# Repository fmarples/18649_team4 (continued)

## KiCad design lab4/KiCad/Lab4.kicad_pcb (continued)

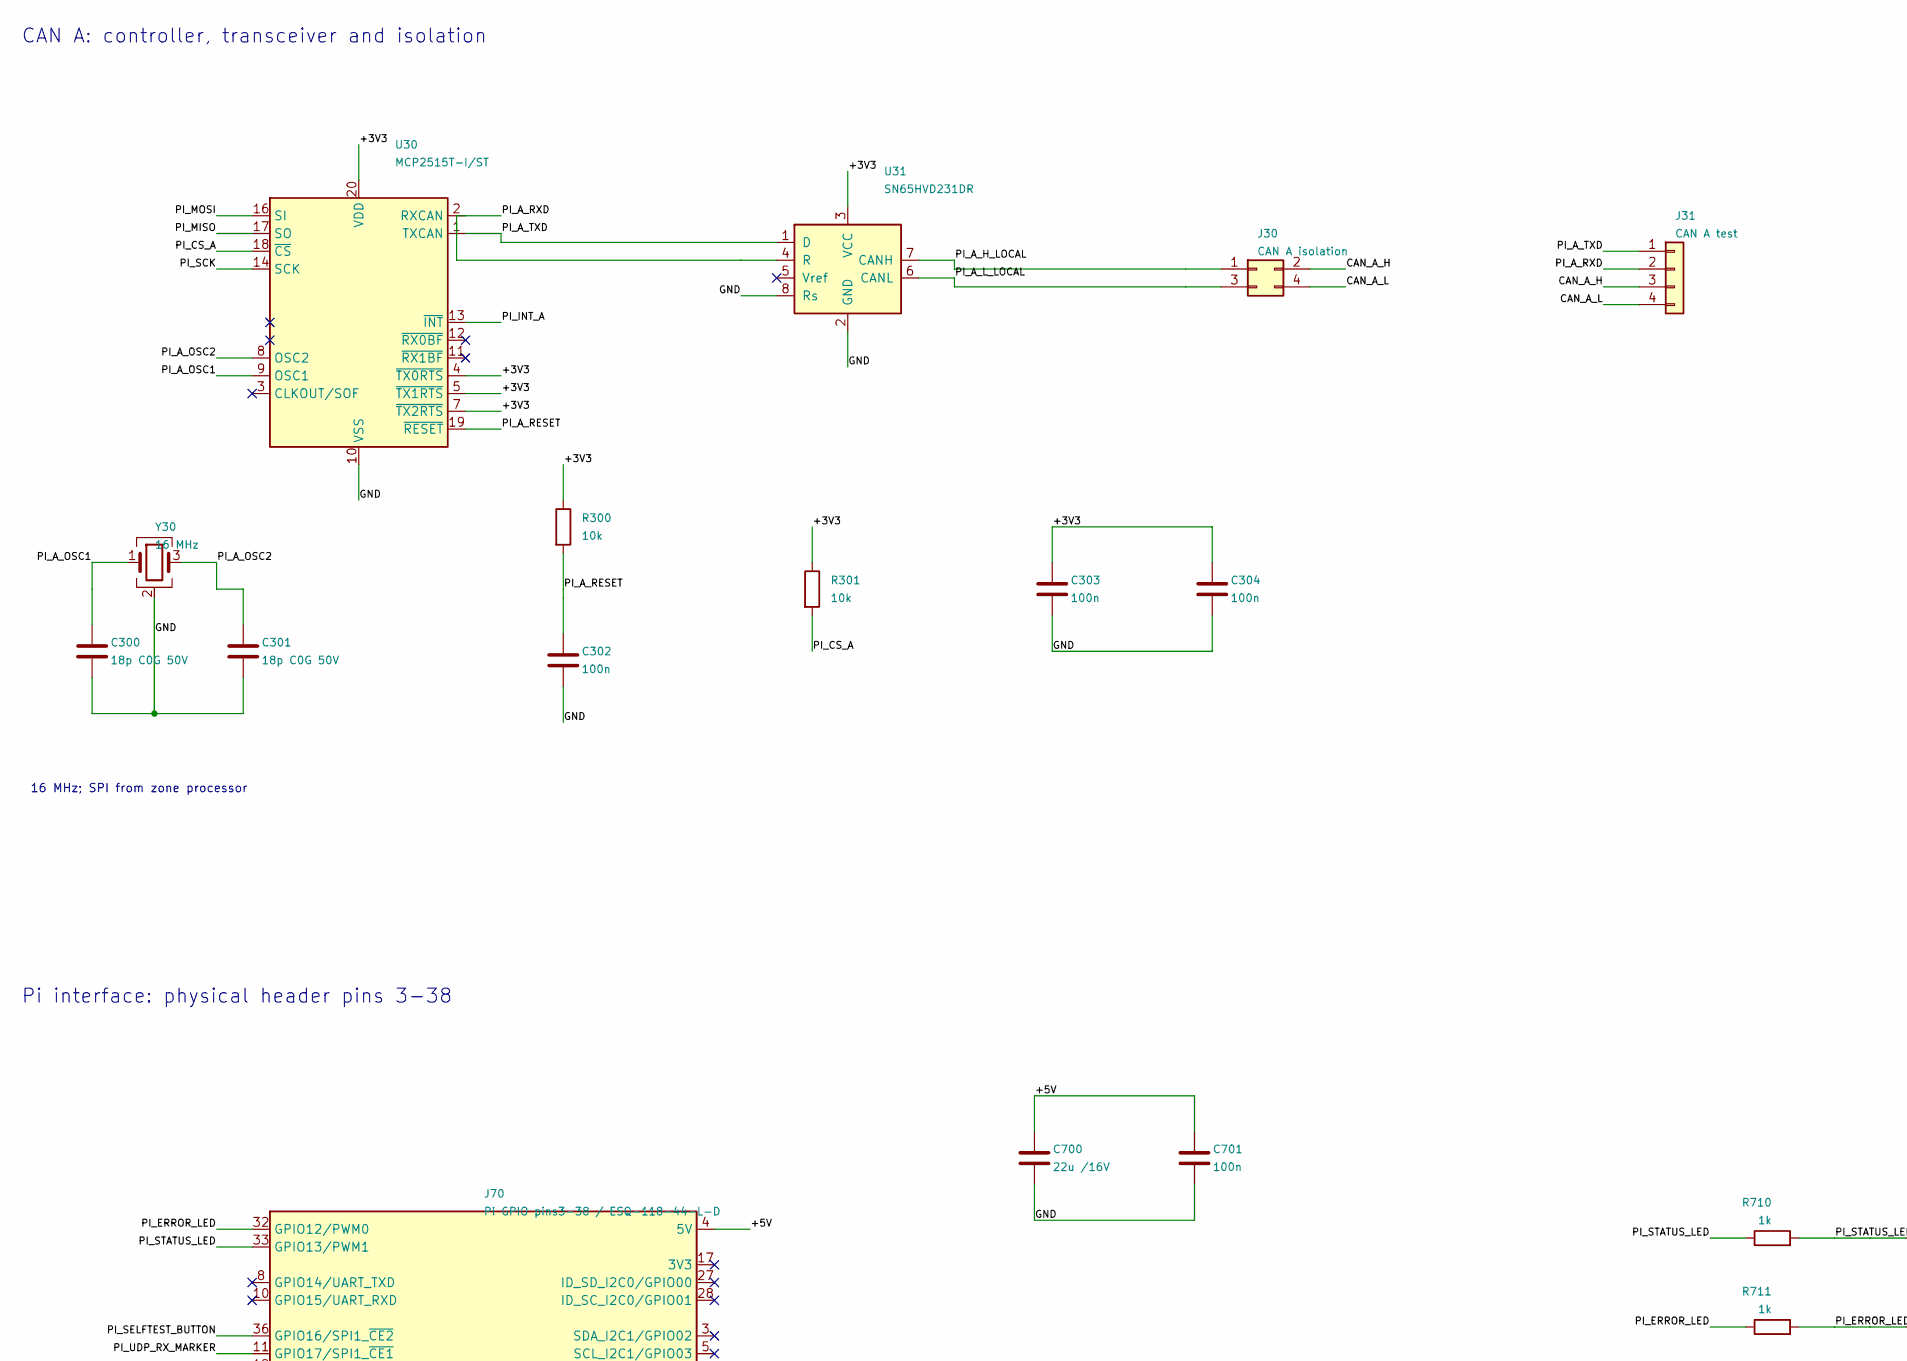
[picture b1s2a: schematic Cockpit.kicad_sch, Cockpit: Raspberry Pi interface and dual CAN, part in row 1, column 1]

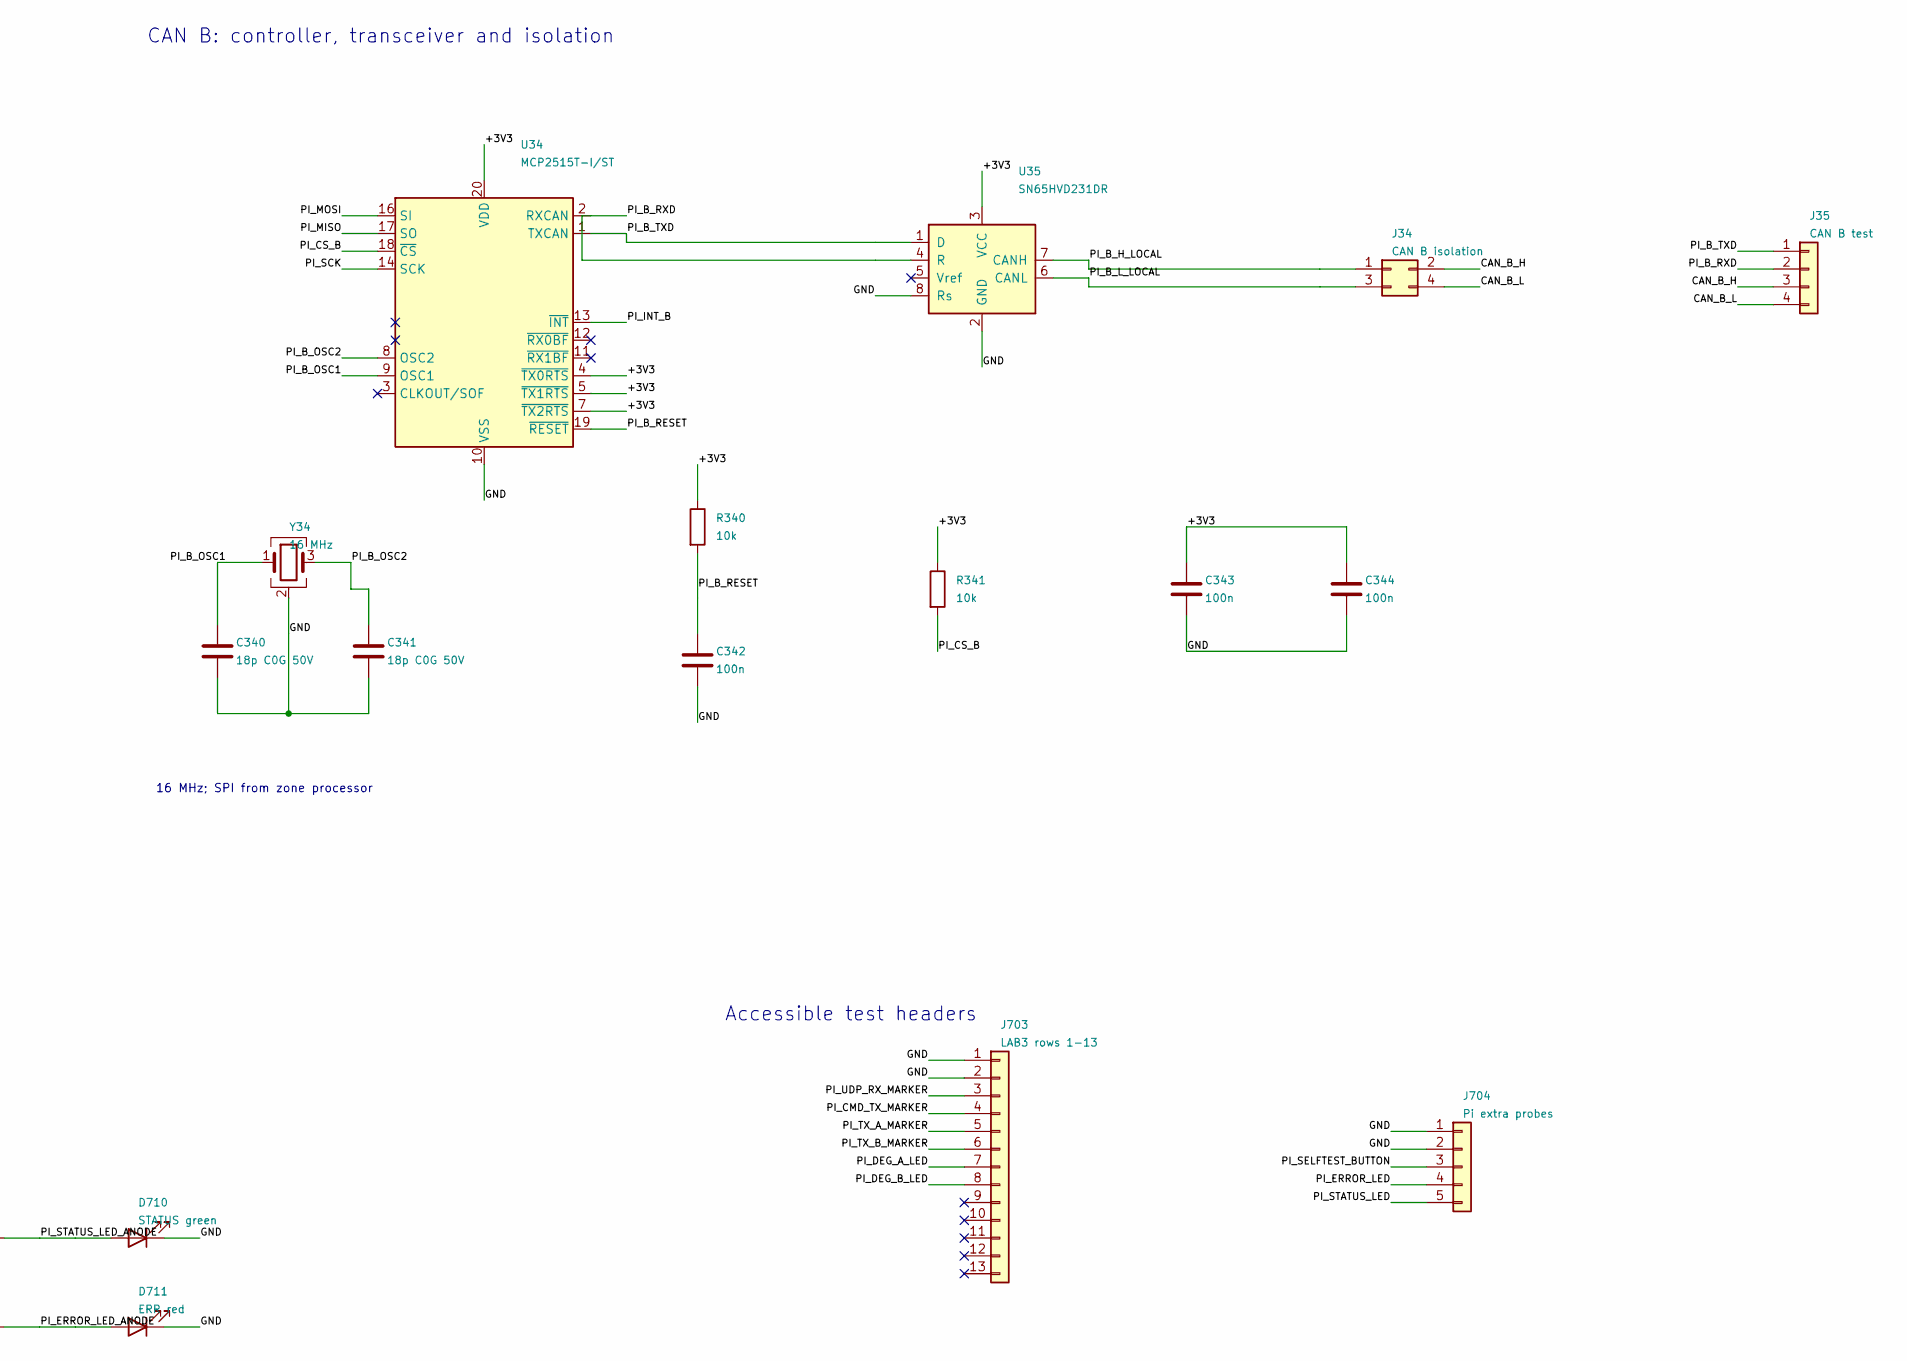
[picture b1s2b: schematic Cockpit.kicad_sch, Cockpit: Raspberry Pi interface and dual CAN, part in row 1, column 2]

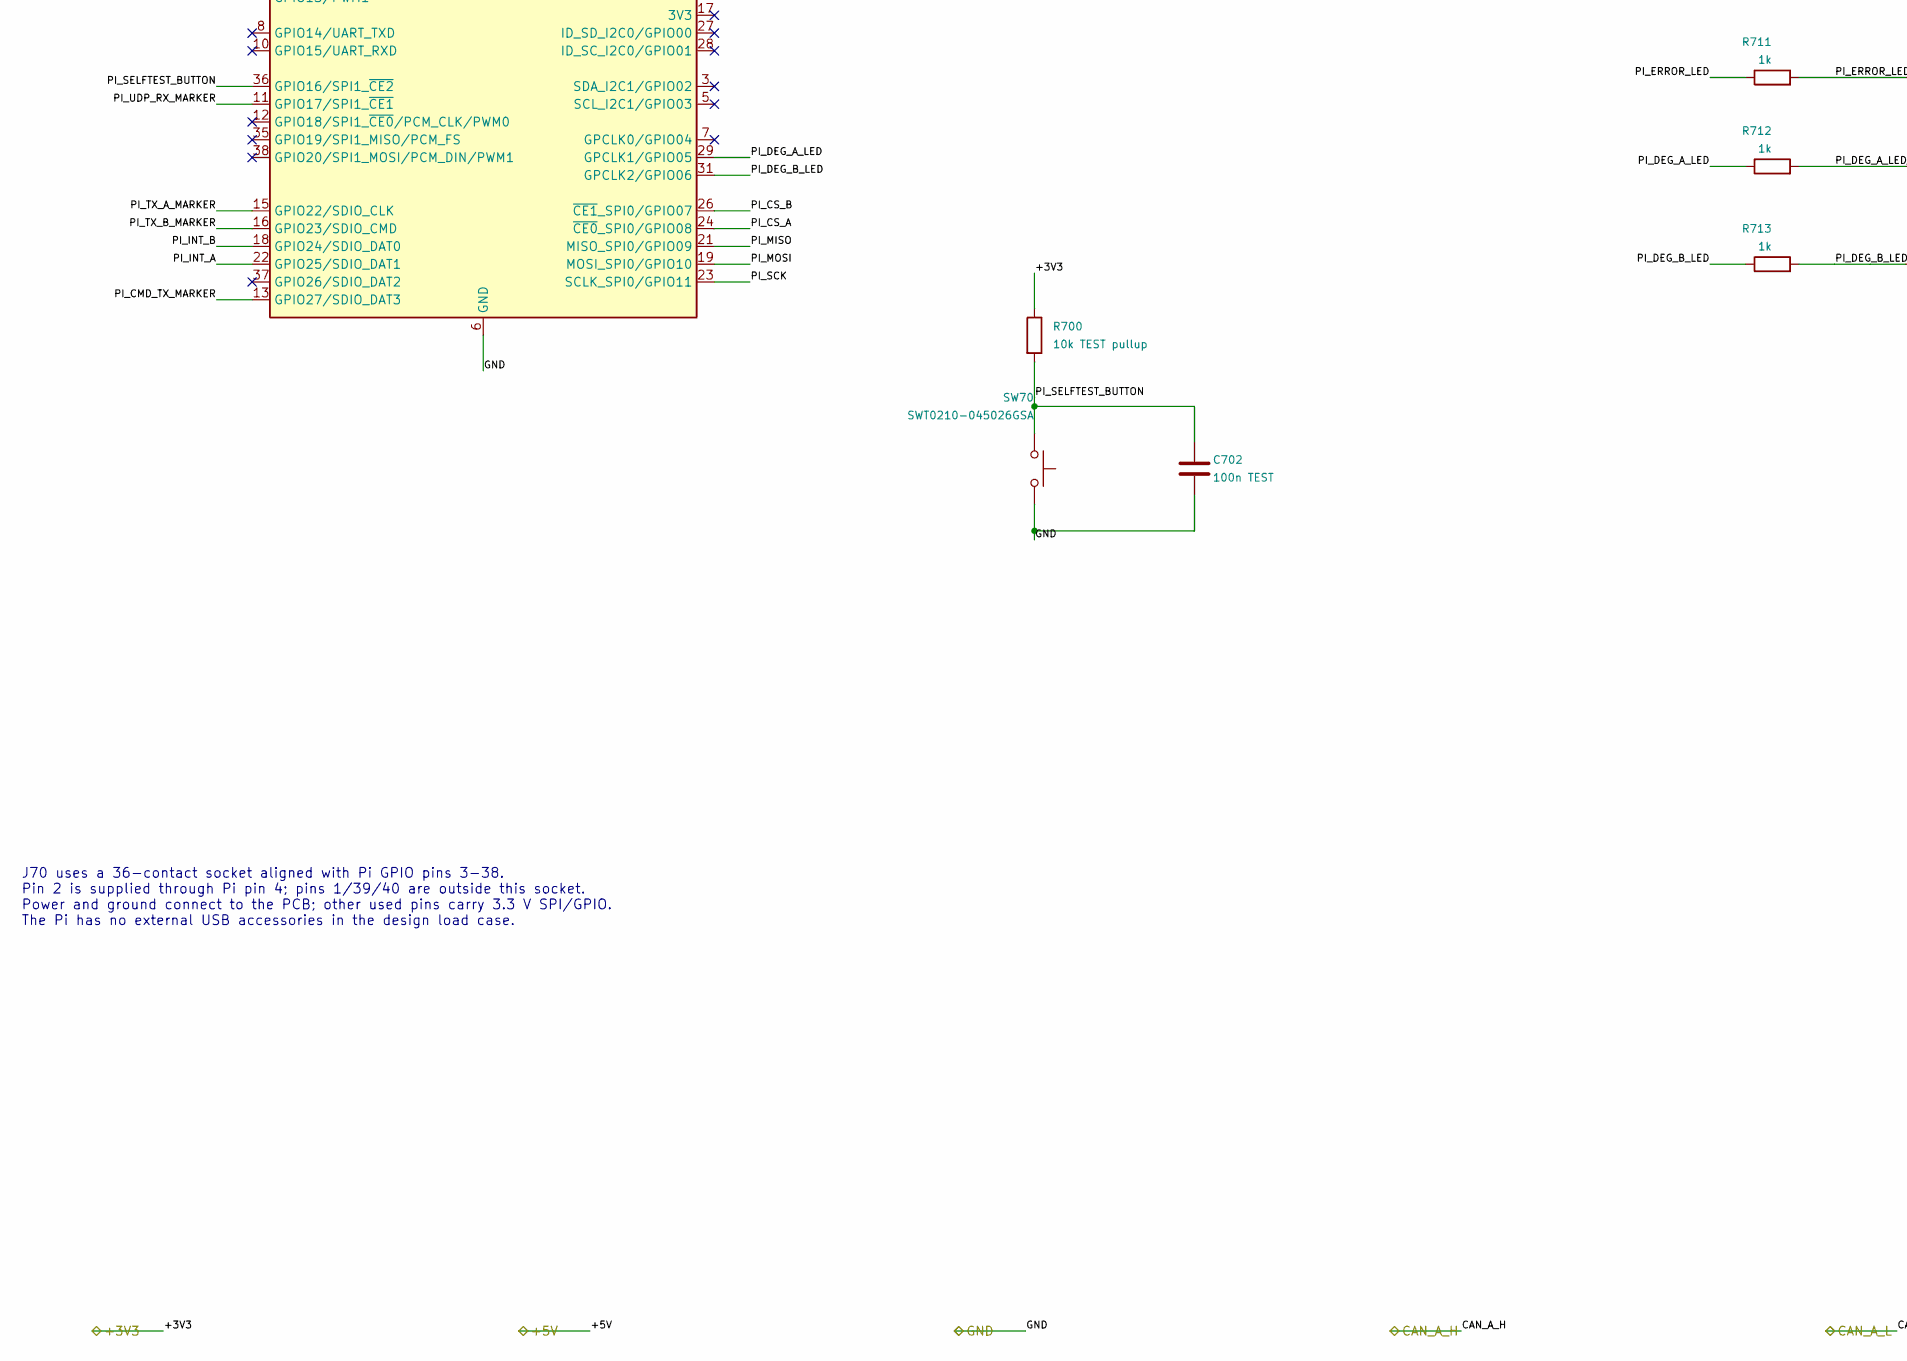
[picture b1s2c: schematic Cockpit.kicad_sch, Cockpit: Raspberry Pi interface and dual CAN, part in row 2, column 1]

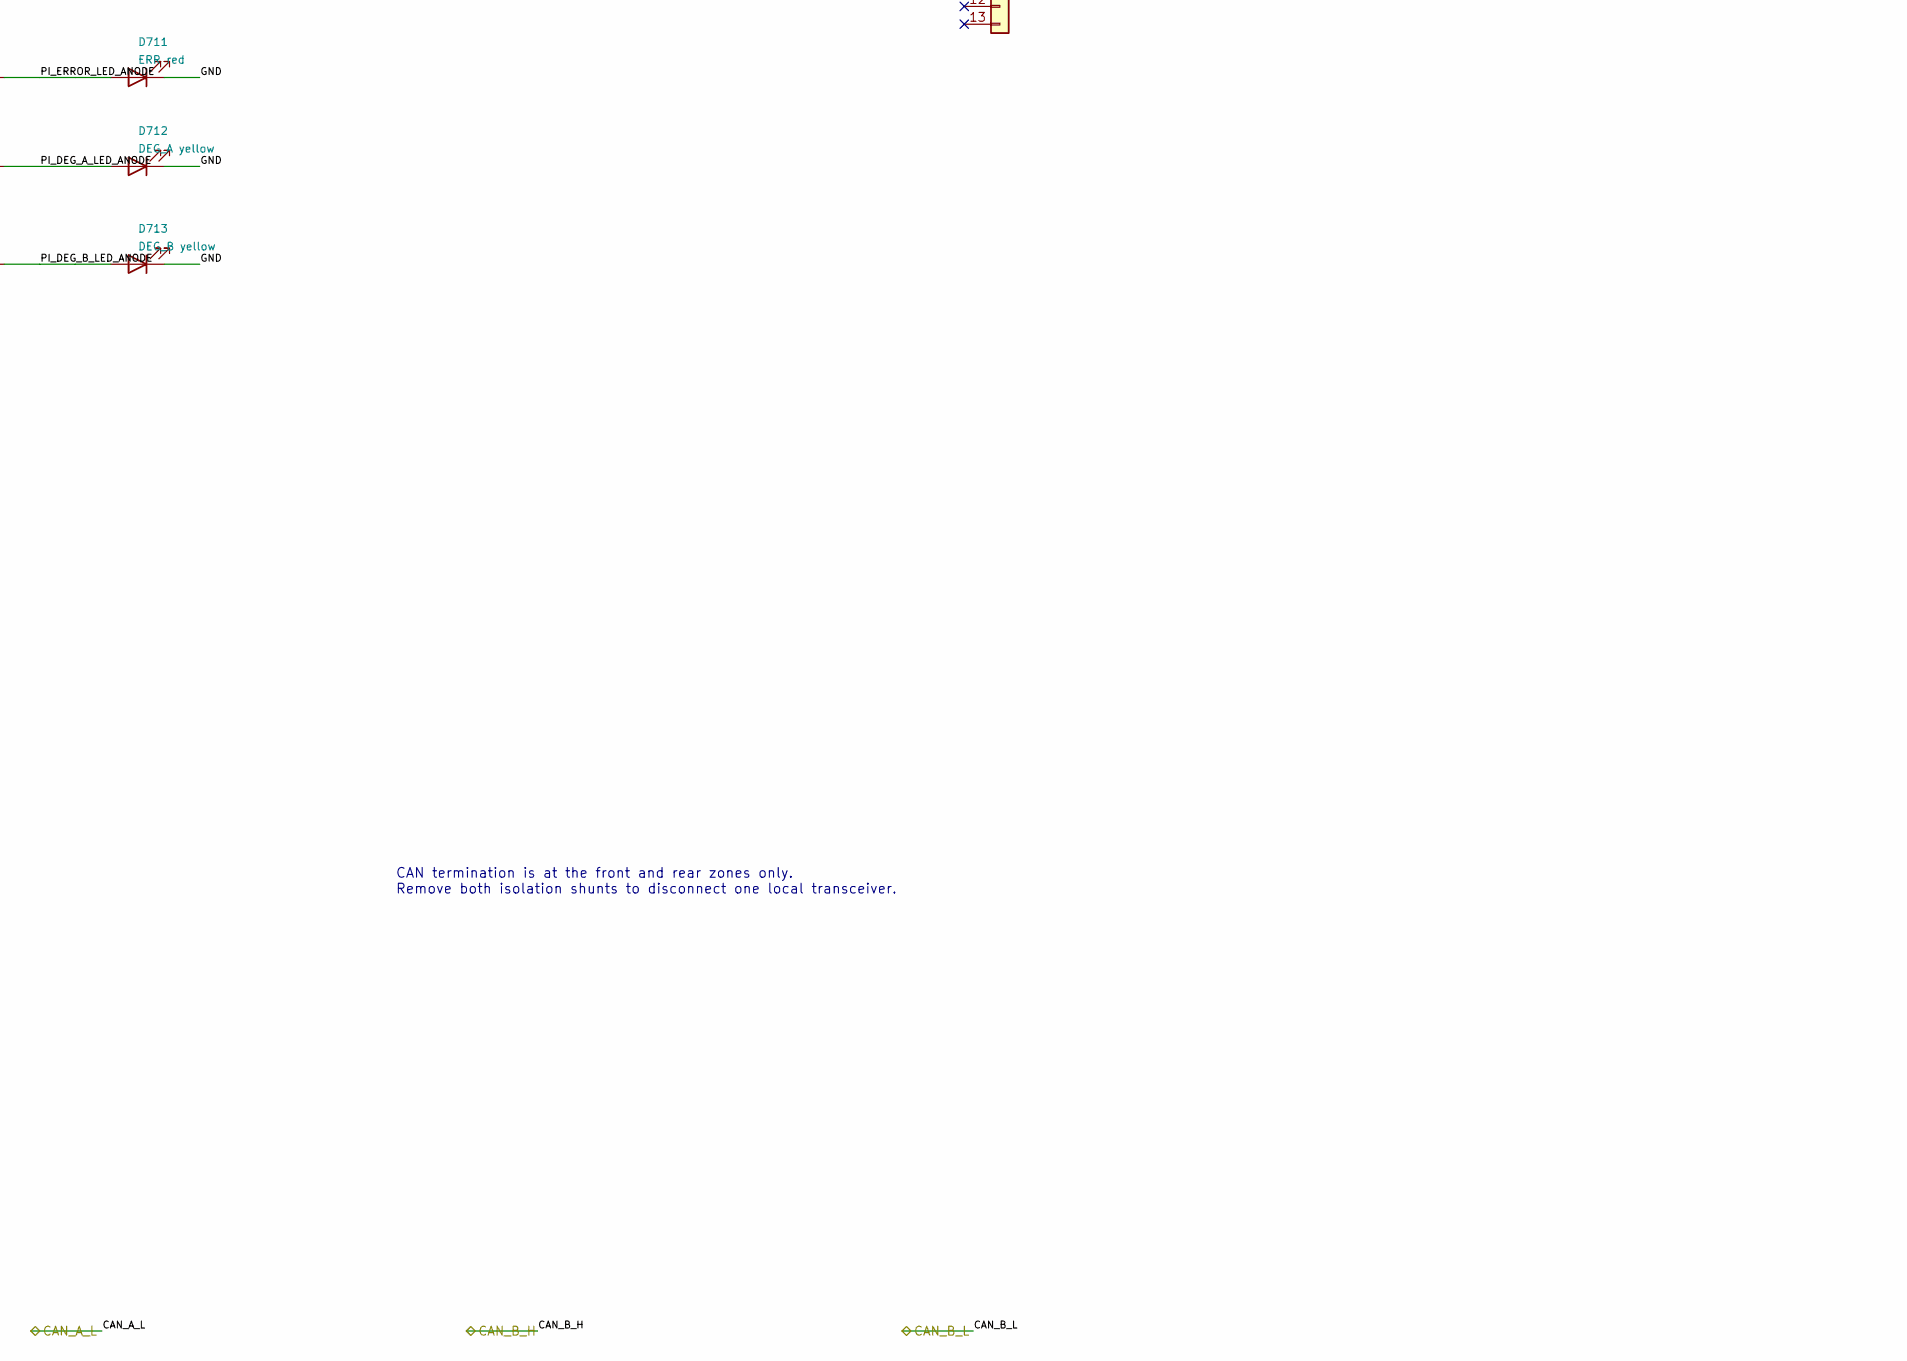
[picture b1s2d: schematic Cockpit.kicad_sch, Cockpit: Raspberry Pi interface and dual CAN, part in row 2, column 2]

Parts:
C300, C301, C340, C341: 18p C0G 50V; C_0603_1608Metric; MPN GRM1885C1H180JA01D
C302, C303, C304, C342, C343, C344, C701: 100n; C_0603_1608Metric; MPN KGM15AR71C104KT
C700: 22u /16V; C_0805_2012Metric; MPN GRM219R61C226ME15L
C702: 100n TEST; C_0603_1608Metric; MPN KGM15AR71C104KT
D710: STATUS green; LED_0603_1608Metric; MPN LTST-C190GKT
D711: ERR red; LED_0603_1608Metric; MPN LTST-C190KRKT
D712: DEG_A yellow; LED_0603_1608Metric; MPN LTST-C190KSKT
D713: DEG_B yellow; LED_0603_1608Metric; MPN LTST-C190KSKT
J30: CAN A isolation; PinHeader_2x02_P2.54mm_Vertical
J31: CAN A test; PinHeader_1x04_P2.54mm_Vertical
J34: CAN B isolation; PinHeader_2x02_P2.54mm_Vertical
J35: CAN B test; PinHeader_1x04_P2.54mm_Vertical
J70: Pi GPIO pins3-38 / ESQ-118-44-L-D; Samtec_ESQ-118-44_2x18_PiPins3-38_H18.67; MPN ESQ-118-44-L-D
J703: LAB3 rows 1-13; PinHeader_1x13_P2.54mm_Vertical; MPN 2.54 mm breakaway header
J704: Pi extra probes; PinHeader_1x05_P2.54mm_Vertical; MPN 2.54 mm breakaway header
R300, R301, R340, R341: 10k; R_0603_1608Metric; MPN CRCW060310K0FKEA
R700: 10k TEST pullup; R_0603_1608Metric; MPN CRCW060310K0FKEA
R710, R711, R712, R713: 1k; R_0603_1608Metric; MPN ERJ-3EKF1001V
SW70: SWT0210-045026GSA; GCT_SWT0210_4.5x4.5mm; MPN SWT0210-045026GSA
U30, U34: MCP2515T-I/ST; TSSOP-20_4.4x6.5mm_P0.65mm; MPN MCP2515T-I/ST
U31, U35: SN65HVD231DR; SOIC-8_3.9x4.9mm_P1.27mm; MPN SN65HVD231DR
Y30, Y34: 16 MHz; Crystal_SMD_3225-4Pin_3.2x2.5mm; MPN CX3225SB16000H0FLJCC

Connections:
/+3V3: C303.1, C304.1, C343.1, C344.1, R300.1, R301.1, R340.1, R341.1, R700.1, U30.4 (~TX0RTS), U30.5 (~TX1RTS), U30.7 (~TX2RTS), U30.20 (VDD), U31.3 (VCC), U34.4 (~TX0RTS), U34.5 (~TX1RTS), U34.7 (~TX2RTS), U34.20 (VDD), U35.3 (VCC); also elsewhere on the board
/+5V: C700.1, C701.1, J70.4 (5V); also elsewhere on the board
/CAN_A_H: J30.2, J31.3; also elsewhere on the board
/CAN_A_L: J30.4, J31.4; also elsewhere on the board
/CAN_B_H: J34.2, J35.3; also elsewhere on the board
/CAN_B_L: J34.4, J35.4; also elsewhere on the board
/Cockpit zone/PI_A_H_LOCAL: J30.1, U31.7 (CANH)
/Cockpit zone/PI_A_L_LOCAL: J30.3, U31.6 (CANL)
/Cockpit zone/PI_A_OSC1: C300.1, U30.9 (OSC1), Y30.1
/Cockpit zone/PI_A_OSC2: C301.1, U30.8 (OSC2), Y30.3
/Cockpit zone/PI_A_RESET: C302.1, R300.2, U30.19 (~RESET)
/Cockpit zone/PI_A_RXD: J31.2, U30.2 (RXCAN), U31.4 (R)
/Cockpit zone/PI_A_TXD: J31.1, U30.1 (TXCAN), U31.1 (D)
/Cockpit zone/PI_B_H_LOCAL: J34.1, U35.7 (CANH)
/Cockpit zone/PI_B_L_LOCAL: J34.3, U35.6 (CANL)
/Cockpit zone/PI_B_OSC1: C340.1, U34.9 (OSC1), Y34.1
/Cockpit zone/PI_B_OSC2: C341.1, U34.8 (OSC2), Y34.3
/Cockpit zone/PI_B_RESET: C342.1, R340.2, U34.19 (~RESET)
/Cockpit zone/PI_B_RXD: J35.2, U34.2 (RXCAN), U35.4 (R)
/Cockpit zone/PI_B_TXD: J35.1, U34.1 (TXCAN), U35.1 (D)
/Cockpit zone/PI_CMD_TX_MARKER: J70.13 (GPIO27/SDIO_DAT3), J703.4
/Cockpit zone/PI_CS_A: J70.24 (~CE0_SPI0/GPIO08), R301.2, U30.18 (~CS)
/Cockpit zone/PI_CS_B: J70.26 (~CE1_SPI0/GPIO07), R341.2, U34.18 (~CS)
/Cockpit zone/PI_DEG_A_LED: J70.29 (GPCLK1/GPIO05), J703.7, R712.1
/Cockpit zone/PI_DEG_A_LED_ANODE: D712.2 (A), R712.2
/Cockpit zone/PI_DEG_B_LED: J70.31 (GPCLK2/GPIO06), J703.8, R713.1
/Cockpit zone/PI_DEG_B_LED_ANODE: D713.2 (A), R713.2
/Cockpit zone/PI_ERROR_LED: J70.32 (GPIO12/PWM0), J704.4, R711.1
/Cockpit zone/PI_ERROR_LED_ANODE: D711.2 (A), R711.2
/Cockpit zone/PI_INT_A: J70.22 (GPIO25/SDIO_DAT1), U30.13 (~INT)
/Cockpit zone/PI_INT_B: J70.18 (GPIO24/SDIO_DAT0), U34.13 (~INT)
/Cockpit zone/PI_MISO: J70.21 (MISO_SPI0/GPIO09), U30.17 (SO), U34.17 (SO)
/Cockpit zone/PI_MOSI: J70.19 (MOSI_SPI0/GPIO10), U30.16 (SI), U34.16 (SI)
/Cockpit zone/PI_SCK: J70.23 (SCLK_SPI0/GPIO11), U30.14 (SCK), U34.14 (SCK)
/Cockpit zone/PI_SELFTEST_BUTTON: C702.1, J70.36 (GPIO16/SPI1_~CE2), J704.3, R700.2, SW70.1
/Cockpit zone/PI_STATUS_LED: J70.33 (GPIO13/PWM1), J704.5, R710.1
/Cockpit zone/PI_STATUS_LED_ANODE: D710.2 (A), R710.2
/Cockpit zone/PI_TX_A_MARKER: J70.15 (GPIO22/SDIO_CLK), J703.5
/Cockpit zone/PI_TX_B_MARKER: J70.16 (GPIO23/SDIO_CMD), J703.6
/Cockpit zone/PI_UDP_RX_MARKER: J70.11 (GPIO17/SPI1_~CE1), J703.3
/GND: C300.2, C301.2, C302.2, C303.2, C304.2, C340.2, C341.2, C342.2, C343.2, C344.2, C700.2, C701.2, C702.2, D710.1 (K), D711.1 (K), D712.1 (K), D713.1 (K), J70.6 (GND), J70.9 (GND), J70.14 (GND), J70.20 (GND), J70.25 (GND), J70.30 (GND), J70.34 (GND), J703.1, J703.2, J704.1, J704.2, SW70.2, U30.10 (VSS), U31.2 (GND), U31.8 (Rs), U34.10 (VSS), U35.2 (GND), U35.8 (Rs), Y30.2 (G), Y30.4 (G), Y34.2 (G), Y34.4 (G); also elsewhere on the board

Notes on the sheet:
CAN A: controller, transceiver and isolation
16 MHz; SPI from zone processor
CAN B: controller, transceiver and isolation
Pi interface: physical header pins 3-38
Accessible test headers
J70 uses a 36-contact socket aligned with Pi GPIO pins 3-38. Pin 2 is supplied through Pi pin 4; pins 1/39/40 are outside this socket. Power and ground connect to the PCB; other used pins carry 3.3 V SPI/GPIO. The Pi has no external USB accessories in the design load case.
CAN termination is at the front and rear zones only. Remove both isolation shunts to disconnect one local transceiver.

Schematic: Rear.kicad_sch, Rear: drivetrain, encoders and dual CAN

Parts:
C3, C5, C6, C8, C202, C203, C204, C242, C243, C244, C801, C803: 100n; C_0603_1608Metric; MPN KGM15AR71C104KT
C4, C7: 1n; C_0603_1608Metric; MPN GCM1885C2A102FA16D
C200, C201, C240, C241: 18p C0G 50V; C_0603_1608Metric; MPN GRM1885C1H180JA01D
C600: 100n VDD19; C_0603_1608Metric; MPN KGM15AR71C104KT
C601: 100n VDD32; C_0603_1608Metric; MPN KGM15AR71C104KT
C602: 100n VDD48; C_0603_1608Metric; MPN KGM15AR71C104KT
C603: 100n VDD64; C_0603_1608Metric; MPN KGM15AR71C104KT
C604: 100n VBAT; C_0603_1608Metric; MPN KGM15AR71C104KT
C605: 4.7u VDD bulk; C_0805_2012Metric; MPN GRM21BR71C475KE51L
C606: 4.7u VCAP1; C_0805_2012Metric; MPN GRM21BR71C475KE51L
C607: 100n VDDA; C_0603_1608Metric; MPN KGM15AR71C104KT
C608: 1u VDDA; C_0603_1608Metric; MPN CC0603JRX7R7BB105
C609: 100n NRST; C_0603_1608Metric; MPN KGM15AR71C104KT
C610: 100n TEST; C_0603_1608Metric; MPN KGM15AR71C104KT
C800: 100n 50V; C_0603_1608Metric; MPN GRM188R71H104KA93D
C802: 470u 25V; CP_Radial_D10.0mm_P5.00mm; MPN EEU-FR1E471
C804, C805: 10u 16V 10% low-ESR; CP_EIA-3528-21_Kemet-B; MPN TPSB106K016R0800
D610: STATUS green; LED_0603_1608Metric; MPN LTST-C190GKT
D611: ERR red; LED_0603_1608Metric; MPN LTST-C190KRKT
D612: DEG_A yellow; LED_0603_1608Metric; MPN LTST-C190KSKT
D613: DEG_B yellow; LED_0603_1608Metric; MPN LTST-C190KSKT
D800, D801, D802, D803, D804, D805, D806, D807: SK520B; D_SMB; MPN SK520B
FB60: 600R @100MHz; L_0603_1608Metric; MPN 742863160
J2, J3: Current test; PinHeader_1x04_P2.54mm_Vertical
J20: CAN A isolation; PinHeader_2x02_P2.54mm_Vertical
J21: CAN A test; PinHeader_1x04_P2.54mm_Vertical
J24: CAN B isolation; PinHeader_2x02_P2.54mm_Vertical
J25: CAN B test; PinHeader_1x04_P2.54mm_Vertical
J80: LEFT motor; Hirose_DF63M-2P-3.96DSA_1x02_P3.96mm_Vertical; MPN DF63M-2P-3.96DSA
J81: RIGHT motor; Hirose_DF63M-2P-3.96DSA_1x02_P3.96mm_Vertical; MPN DF63M-2P-3.96DSA
J82: LEFT encoder; PinHeader_1x04_P2.54mm_Vertical; MPN 2.54 mm breakaway header
J83: RIGHT encoder; PinHeader_1x04_P2.54mm_Vertical; MPN 2.54 mm breakaway header
J600: BOOT recovery; PinHeader_1x02_P2.54mm_Vertical; MPN 2.54 mm breakaway header
J601: SWD (2.54mm); PinHeader_1x06_P2.54mm_Vertical; MPN 2.54 mm breakaway header
J602: 3.3V TTL UART; PinHeader_1x03_P2.54mm_Vertical; MPN 2.54 mm breakaway header
J603: LAB3 rows 1-13; PinHeader_1x13_P2.54mm_Vertical; MPN 2.54 mm breakaway header
J604: Additional probes; PinHeader_1x11_P2.54mm_Vertical; MPN 2.54 mm breakaway header
J605: Reserved / encoder probes; PinHeader_1x07_P2.54mm_Vertical; MPN 2.54 mm breakaway header
J650: REAR LEFT lamp; PinHeader_1x02_P2.54mm_Vertical; MPN 2.54 mm breakaway header
J651: REAR RIGHT lamp; PinHeader_1x02_P2.54mm_Vertical; MPN 2.54 mm breakaway header
JP20: TERM A; PinHeader_1x02_P2.54mm_Vertical
JP24: TERM B; PinHeader_1x02_P2.54mm_Vertical
Q650, Q651: MMBT3904; SOT-23; MPN MMBT3904-7-F
R3, R4, R6, R7, R200, R201, R240, R241, R804, R805, R806, R807: 10k; R_0603_1608Metric; MPN CRCW060310K0FKEA
R5, R8, R610, R611, R612, R613: 1k; R_0603_1608Metric; MPN ERJ-3EKF1001V
R202, R242: 120R; R_0603_1608Metric; MPN RC0603FR-07120RL
R600: 10k BOOT0; R_0603_1608Metric; MPN CRCW060310K0FKEA
R601: 10k NRST; R_0603_1608Metric; MPN CRCW060310K0FKEA
R602: 10k TEST pullup; R_0603_1608Metric; MPN CRCW060310K0FKEA
R630, R631, R632, R633, R634, R635: 10k boot pulldown; R_0603_1608Metric; MPN CRCW060310K0FKEA
R650, R651: 2.2k; R_0603_1608Metric; MPN CRCW06032K20FKEA
R660, R661: 100k; R_0603_1608Metric; MPN CRCW0603100KFKEA
R670, R671: 220R; R_0603_1608Metric; MPN CRCW0603220RFKEA
R800, R801, R802, R803: 100R; R_0603_1608Metric; MPN CRCW0603100RFKEA
SW60, SW61: SWT0210-045026GSA; GCT_SWT0210_4.5x4.5mm; MPN SWT0210-045026GSA
U2, U3: ACS712ELCTR-05B-T; SOIC-8_3.9x4.9mm_P1.27mm; MPN ACS712ELCTR-05B-T
U20, U24: MCP2515T-I/ST; TSSOP-20_4.4x6.5mm_P0.65mm; MPN MCP2515T-I/ST
U21, U25: SN65HVD231DR; SOIC-8_3.9x4.9mm_P1.27mm; MPN SN65HVD231DR
U60: STM32F401RET6TR; LQFP-64_10x10mm_P0.5mm; MPN STM32F401RET6TR
U80: L298N; ST_L298N_Multiwatt15V_D1.1; MPN L298N
U81: SN74LVC14APWR; TSSOP-14_4.4x5mm_P0.65mm; MPN SN74LVC14APWR
U82: MCP1700-4002E/TO; TO-92_Inline_Wide; MPN MCP1700-4002E/TO
Y20, Y24: 16 MHz; Crystal_SMD_3225-4Pin_3.2x2.5mm; MPN CX3225SB16000H0FLJCC

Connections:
/+3V3: C203.1, C204.1, C243.1, C244.1, C600.1, C601.1, C602.1, C603.1, C604.1, C605.1, C803.1, FB60.1, J600.1, J601.1, R200.1, R201.1, R240.1, R241.1, R601.1, R602.1, R804.1, R805.1, R806.1, R807.1, U20.4 (~TX0RTS), U20.5 (~TX1RTS), U20.7 (~TX2RTS), U20.20 (VDD), U21.3 (VCC), U24.4 (~TX0RTS), U24.5 (~TX1RTS), U24.7 (~TX2RTS), U24.20 (VDD), U25.3 (VCC), U60.1 (VBAT), U60.19 (VDD), U60.32 (VDD), U60.48 (VDD), U60.64 (VDD), U81.14 (VCC); also elsewhere on the board
/+5V: C3.1, C6.1, C801.1, C804.1, R670.1, R671.1, U2.8 (VCC), U3.8 (VCC), U80.9 (Vss), U82.2 (VI); also elsewhere on the board
/CAN_A_H: J20.2, J21.3, JP20.1 (A); also elsewhere on the board
/CAN_A_L: J20.4, J21.4, R202.2; also elsewhere on the board
/CAN_B_H: J24.2, J25.3, JP24.1 (A); also elsewhere on the board
/CAN_B_L: J24.4, J25.4, R242.2; also elsewhere on the board
/GND: C3.2, C4.2, C5.2, C6.2, C7.2, C8.2, C200.2, C201.2, C202.2, C203.2, C204.2, C240.2, C241.2, C242.2, C243.2, C244.2, C600.2, C601.2, C602.2, C603.2, C604.2, C605.2, C606.2, C607.2, C608.2, C609.2, C610.2, C800.2, C801.2, C802.2, C803.2, C804.2, C805.2, D610.1 (K), D611.1 (K), D612.1 (K), D613.1 (K), D801.2 (A), D803.2 (A), D805.2 (A), D807.2 (A), J2.4, J3.4, J82.2, J83.2, J601.3, J601.6, J602.3, J603.1, J603.2, J604.1, J604.2, J605.1, J605.2, Q650.2 (E), Q651.2 (E), R4.2, R7.2, R600.2, R630.2, R631.2, R632.2, R633.2, R634.2, R635.2, R660.2, R661.2, SW60.2, SW61.2, U2.5 (GND), U3.5 (GND), U20.10 (VSS), U21.2 (GND), U21.8 (Rs), U24.10 (VSS), U25.2 (GND), U25.8 (Rs), U60.12 (VSSA), U60.18 (VSS), U60.31 (VSS), U60.47 (VSS), U60.63 (VSS), U80.1 (SENSE_A), U80.8 (GND), U80.15 (SENSE_B), U81.7 (GND), U81.11 (5A), U81.13 (6A), U82.1 (GND), Y20.2 (G), Y20.4 (G), Y24.2 (G), Y24.4 (G); also elsewhere on the board
/Rear zone/ENC_4V: C805.1, J82.1, J83.1, U82.3 (VO)
/Rear zone/LEFT_ADC: C5.1, J2.3, J604.10, R5.2, U60.16 (PA2)
/Rear zone/LEFT_BRIDGE: U2.1 (IP+), U2.2 (IP+), U80.2 (OUT1)
/Rear zone/LEFT_ENC_A_IN: R800.2, U81.1 (1A)
/Rear zone/LEFT_ENC_A_RAW: J82.3, R800.1, R804.2
/Rear zone/LEFT_ENC_B_IN: R801.2, U81.3 (2A)
/Rear zone/LEFT_ENC_B_RAW: J82.4, R801.1, R805.2
/Rear zone/LEFT_FILTER: C4.1, U2.6 (FILTER)
/Rear zone/LEFT_MOTOR: D800.2 (A), D801.1 (K), J80.1, U2.3 (IP-), U2.4 (IP-)
/Rear zone/LEFT_RAW: J2.1, R3.1, U2.7 (VIOUT)
/Rear zone/LEFT_RETURN: D802.2 (A), D803.1 (K), J80.2, U80.3 (OUT2)
/Rear zone/LEFT_SCALED: J2.2, R3.2, R4.1, R5.1
/Rear zone/RIGHT_ADC: C8.1, J3.3, J604.11, R8.2, U60.17 (PA3)
/Rear zone/RIGHT_BRIDGE: U3.1 (IP+), U3.2 (IP+), U80.13 (OUT3)
/Rear zone/RIGHT_ENC_A_IN: R802.2, U81.5 (3A)
/Rear zone/RIGHT_ENC_A_RAW: J83.3, R802.1, R806.2
/Rear zone/RIGHT_ENC_B_IN: R803.2, U81.9 (4A)
/Rear zone/RIGHT_ENC_B_RAW: J83.4, R803.1, R807.2
/Rear zone/RIGHT_FILTER: C7.1, U3.6 (FILTER)
/Rear zone/RIGHT_MOTOR: D804.2 (A), D805.1 (K), J81.1, U3.3 (IP-), U3.4 (IP-)
/Rear zone/RIGHT_RAW: J3.1, R6.1, U3.7 (VIOUT)
/Rear zone/RIGHT_RETURN: D806.2 (A), D807.1 (K), J81.2, U80.14 (OUT4)
/Rear zone/RIGHT_SCALED: J3.2, R6.2, R7.1, R8.1
/Rear zone/R_A_H_LOCAL: J20.1, U21.7 (CANH)
/Rear zone/R_A_L_LOCAL: J20.3, U21.6 (CANL)
/Rear zone/R_A_OSC1: C200.1, U20.9 (OSC1), Y20.1
/Rear zone/R_A_OSC2: C201.1, U20.8 (OSC2), Y20.3
/Rear zone/R_A_RESET: C202.1, R200.2, U20.19 (~RESET)
/Rear zone/R_A_RXD: J21.2, U20.2 (RXCAN), U21.4 (R)
/Rear zone/R_A_TERM: JP20.2 (B), R202.1
/Rear zone/R_A_TXD: J21.1, U20.1 (TXCAN), U21.1 (D)
/Rear zone/R_BOOT0: J600.2, R600.1, U60.60 (BOOT0)
/Rear zone/R_B_H_LOCAL: J24.1, U25.7 (CANH)
/Rear zone/R_B_L_LOCAL: J24.3, U25.6 (CANL)
/Rear zone/R_B_OSC1: C240.1, U24.9 (OSC1), Y24.1
/Rear zone/R_B_OSC2: C241.1, U24.8 (OSC2), Y24.3
/Rear zone/R_B_RESET: C242.1, R240.2, U24.19 (~RESET)
/Rear zone/R_B_RXD: J25.2, U24.2 (RXCAN), U25.4 (R)
/Rear zone/R_B_TERM: JP24.2 (B), R242.1
/Rear zone/R_B_TXD: J25.1, U24.1 (TXCAN), U25.1 (D)
/Rear zone/R_CS_A: R201.2, U20.18 (~CS), U60.58 (PB6)
/Rear zone/R_CS_B: R241.2, U24.18 (~CS), U60.38 (PC7)
/Rear zone/R_DEG_A_LED: J603.7, R612.1, U60.26 (PB0)
/Rear zone/R_DEG_A_LED_ANODE: D612.2 (A), R612.2
/Rear zone/R_DEG_B_LED: J603.8, R613.1, U60.27 (PB1)
/Rear zone/R_DEG_B_LED_ANODE: D613.2 (A), R613.2
/Rear zone/R_DIR_A_MARKER: J603.11, U60.29 (PB10)
/Rear zone/R_ERROR_LED: J604.4, R611.1, U60.8 (PC0)
/Rear zone/R_ERROR_LED_ANODE: D611.2 (A), R611.2
/Rear zone/R_INT_A: U20.13 (~INT), U60.43 (PA10)
/Rear zone/R_INT_B: U24.13 (~INT), U60.57 (PB5)
/Rear zone/R_LEFT_ENABLE_PWM: J603.10, R630.1, U60.42 (PA9), U80.6 (EnA)
/Rear zone/R_LEFT_ENC_A: J605.3, U60.28 (PB2), U81.2 (1Y)
/Rear zone/R_LEFT_ENC_B: J605.4, U60.55 (PB3), U81.4 (2Y)
/Rear zone/R_LEFT_IN1: R632.1, U60.34 (PB13), U80.5 (IN1)
/Rear zone/R_LEFT_IN2: R633.1, U60.35 (PB14), U80.7 (IN2)
/Rear zone/R_MISO: U20.17 (SO), U24.17 (SO), U60.22 (PA6)
/Rear zone/R_MOSI: U20.16 (SI), U24.16 (SI), U60.23 (PA7)
/Rear zone/R_OVERLOAD_MARKER: J604.9, U60.52 (PC11)
/Rear zone/R_PID_MARKER: J604.7, U60.40 (PC9)
/Rear zone/R_PWM_SET_MARKER: J603.9, U60.62 (PB9)
/Rear zone/R_REAR_LEFT_LED: J603.12, R650.1, U60.24 (PC4)
/Rear zone/R_REAR_LEFT_LED_BASE: Q650.1 (B), R650.2, R660.1
/Rear zone/R_REAR_LEFT_LED_PLUS: J650.1, R670.2
/Rear zone/R_REAR_LEFT_LED_SINK: J650.2, Q650.3 (C)
/Rear zone/R_REAR_RIGHT_LED: J603.13, R651.1, U60.25 (PC5)
/Rear zone/R_REAR_RIGHT_LED_BASE: Q651.1 (B), R651.2, R661.1
/Rear zone/R_REAR_RIGHT_LED_PLUS: J651.1, R671.2
/Rear zone/R_REAR_RIGHT_LED_SINK: J651.2, Q651.3 (C)
/Rear zone/R_RELAY_TX_MARKER: J605.7, U60.37 (PC6)
/Rear zone/R_RESET_N: C609.1, J601.5, R601.2, SW60.1, U60.7 (NRST)
/Rear zone/R_RIGHT_ENABLE_PWM: J604.8, R631.1, U60.59 (PB7), U80.11 (EnB)
/Rear zone/R_RIGHT_ENC_A: J605.5, U60.56 (PB4), U81.6 (3Y)
/Rear zone/R_RIGHT_ENC_B: J605.6, U60.33 (PB12), U81.8 (4Y)
/Rear zone/R_RIGHT_IN3: R634.1, U60.36 (PB15), U80.10 (IN3)
/Rear zone/R_RIGHT_IN4: R635.1, U60.51 (PC10), U80.12 (IN4)
/Rear zone/R_RX_A_MARKER: J603.3, U60.10 (PC2)
/Rear zone/R_RX_B_MARKER: J603.4, U60.11 (PC3)
/Rear zone/R_SCK: U20.14 (SCK), U24.14 (SCK), U60.21 (PA5)
/Rear zone/R_SELFTEST_BUTTON: C610.1, J604.3, R602.2, SW61.1, U60.2 (PC13)
/Rear zone/R_STATUS_LED: R610.1, U60.50 (PA15)
/Rear zone/R_STATUS_LED_ANODE: D610.2 (A), R610.2
/Rear zone/R_STEER_TASK_MARKER: J604.6, U60.9 (PC1)
/Rear zone/R_SWCLK: J601.2, U60.49 (PA14)
/Rear zone/R_SWDIO: J601.4, U60.46 (PA13)
/Rear zone/R_TASK_PROBE: J604.5, U60.39 (PC8)
/Rear zone/R_TX_A_MARKER: J603.5, U60.14 (PA0)
/Rear zone/R_TX_B_MARKER: J603.6, U60.15 (PA1)
/Rear zone/R_UART_CONSOLE_RX: J602.2, U60.45 (PA12)
/Rear zone/R_UART_CONSOLE_TX: J602.1, U60.44 (PA11)
/Rear zone/R_VCAP1: C606.1, U60.30 (VCAP1)
/Rear zone/R_VDDA: C607.1, C608.1, FB60.2, U60.13 (VREF+)
/VBAT_PROTECTED: C800.1, C802.1, D800.1 (K), D802.1 (K), D804.1 (K), D806.1 (K), U80.4 (Vs); also elsewhere on the board

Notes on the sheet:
CAN A: controller, transceiver and isolation
16 MHz; SPI from zone processor
CAN B: controller, transceiver and isolation
STM32F401: processor, supplies and recovery
100 nF at each VDD pin; VCAP is a dedicated regulator output.
Motor H-bridge / output clamps / connectors
All flyback clamps are on the motor side of the ACS712. Recirculation can bypass the sensor; telemetry is not complete phase current.
Left motor current / ADC filter
Right motor current / ADC filter
Encoder power / 5 V-tolerant Schmitt inputs
Vehicle lamps
Accessible test headers
